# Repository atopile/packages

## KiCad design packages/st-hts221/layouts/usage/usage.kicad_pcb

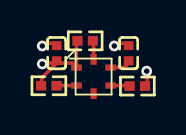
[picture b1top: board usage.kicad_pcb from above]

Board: 2 copper layers, 6 parts (0 on the bottom side), 5 nets.

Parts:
C1: 100nF; C0402
C2: 10µF; C0402
R2, R3, R4: 10kΩ; R0402
U1: HLGA-6L_L2.0-M2.0-P1.00-TL

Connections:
CS: R2.2, U1.6
SCL: R3.1, U1.2
SDA: R4.1, U1.4
hv: C1.1, C2.1, R2.1, R3.2, R4.2, U1.1
lv: C1.2, C2.2, U1.5

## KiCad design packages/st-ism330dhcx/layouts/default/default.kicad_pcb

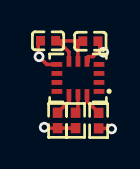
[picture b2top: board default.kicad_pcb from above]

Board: 2 copper layers, 6 parts (0 on the bottom side), 6 nets.

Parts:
C1, C2: 0F; C0402
R1, R2, R3: 10000Ω; R0402
U1: LGA-14_L3.0-W2.5-P0.50-BR

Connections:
CS: R1.2, U1.12
SCL: R2.1, U1.13
decoupling_caps[0]-power-hv: C1.1, U1.8
hv: C2.1, R1.1, R2.2, R3.2, U1.5
lv: C1.2, C2.2, U1.1, U1.6, U1.7
spi-MOSI: R3.1, U1.14

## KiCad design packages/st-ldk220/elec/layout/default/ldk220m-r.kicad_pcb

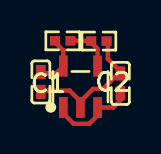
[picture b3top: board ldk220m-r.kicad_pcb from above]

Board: 2 copper layers, 5 parts (0 on the bottom side), 4 nets.

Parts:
C1, C2: 1µF ±10% 25V X5R; C0402-b3ef17
R1: 18kΩ ±1% 62.5mW; R0402-56259e
R2: 10kΩ ±1% 62.5mW; R0402-56259e
U1: SOT-23-5_L3.0-W1.7-P0.95-LS2.8-BL

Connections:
ADJ_NC: R1.2, R2.1, U1.4
IN: C1.1, U1.1, U1.3
OUT: C2.1, R1.1, U1.5
gnd: C1.2, C2.2, R2.2, U1.2
